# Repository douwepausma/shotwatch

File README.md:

# Shotwatch
Display the brewing time of your GAGGIA Classic Pro with Shotwatch ☕️⏱️. This handy DIY gadget allows to display the amount of seconds your GAGGIA has been running on display.
>'Shotwatch' is a combination of the words 'Espresso <ins>**Shot**</ins>' and 'Stop<ins>**watch**</ins>'

## Why?
Many times I've either forgot to start counting our lost count (counting till 20 is hard okay) for how long my shot was running for. So I thought 'why not make something that does this for me?' After some Googling I quickly found solutions to this problem online, ones that I could purchase and install myself. They were however quite expensive, and this project sounded like something I could handle myself and learn a thing or two. So I opted to do it myself. In the end I probably spend more time and money prototyping then when I would've bought a solution, but what's the fun in that?! And (spoiler alert) I even learned how to make my own pcb in this project!

## How does it work?
The Shotwatch is quite simple and consists out of only 2 components, the screen and the logic board. The logic board is hooked up in series with two wires behind the brewing switch, this turns the Shotwatch on and automatically starts counting. The number is displayed on a small OLED screen connected to the logic board. Logic board is an Arduino Pro Micro, and powered with current directly coming via the brewing switch itself. GAGGIA Classic Pro's internals are all 230 AC current, so the I created a pcb where the logic board is mounted onto that houses a transformer to get the appropriate volts and wattage.

## Bill of materials
In addition to the 3 printed parts and the Shotwatch PCB, the following parts are required. You can find all the parts below on AliExpress. Concerning the Shotwatch PCB, you can get this manufactured at PCBWay with the gerber files. And you can print the STL files for the case yourself, or find a place where you can get them printed.

|Part|Amount|
|----|------|
|HLK-10M05(10W 5V)|1x|
|Arduino Pro Micro|1x|
|Header pins 2x12|2x|
|SSD1315 Oled screen|1x|
|4pin JST female connector|1x|
|4pin JST male connector|2x|
|KF128 5.08MM pitch, 2 port screw terminal|1x|
|30cm 4 wire ribbon cable|1x|
|30cm 18 AWG cable|2x|
|Piggyback connecter (with insulation)|2x|

## Assembly
https://github.com/user-attachments/assets/8fb99642-29bd-4e3d-afc3-6cd245b8583b

## Shotwatch in action
https://github.com/user-attachments/assets/95962a83-e972-49d3-940f-4a79777042f4

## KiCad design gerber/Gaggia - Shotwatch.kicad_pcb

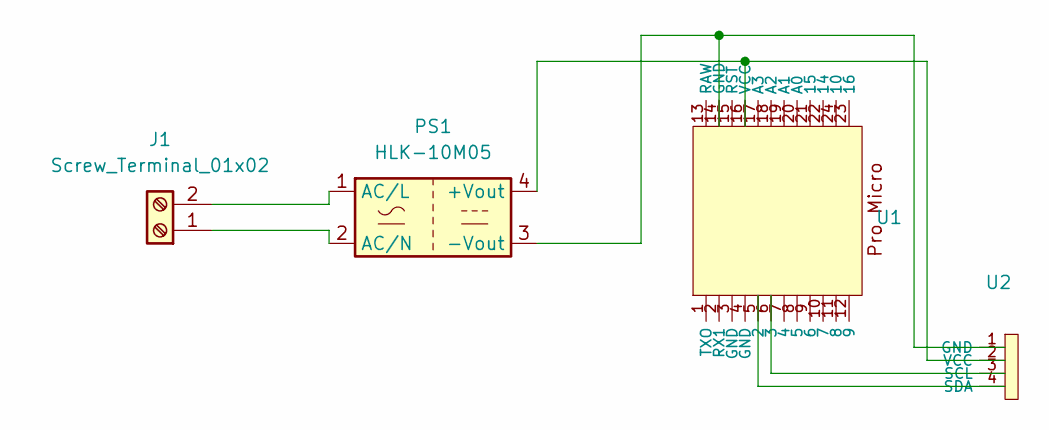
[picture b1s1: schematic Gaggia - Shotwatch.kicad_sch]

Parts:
J1: Screw_Terminal_01x02; TerminalBlock_MaiXu_MX126-5.0-02P_1x02_P5.00mm
PS1: HLK-10M05; Converter_ACDC_Hi-Link_HLK-10Mxx
U1: Pro Micro
U2: 4_Through_Hole_Pads

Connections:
unnamed: J1.1, PS1.2 (AC/N)
unnamed: J1.2, PS1.1 (AC/L)
unnamed: PS1.4 (+Vout), U1.16 (VCC), U2.2 (VCC)
unnamed: PS1.3 (-Vout), U1.14 (GND), U2.1 (GND)
unnamed: U1.5 (2), U2.4 (SDA)
unnamed: U1.6 (3), U2.3 (SCL)

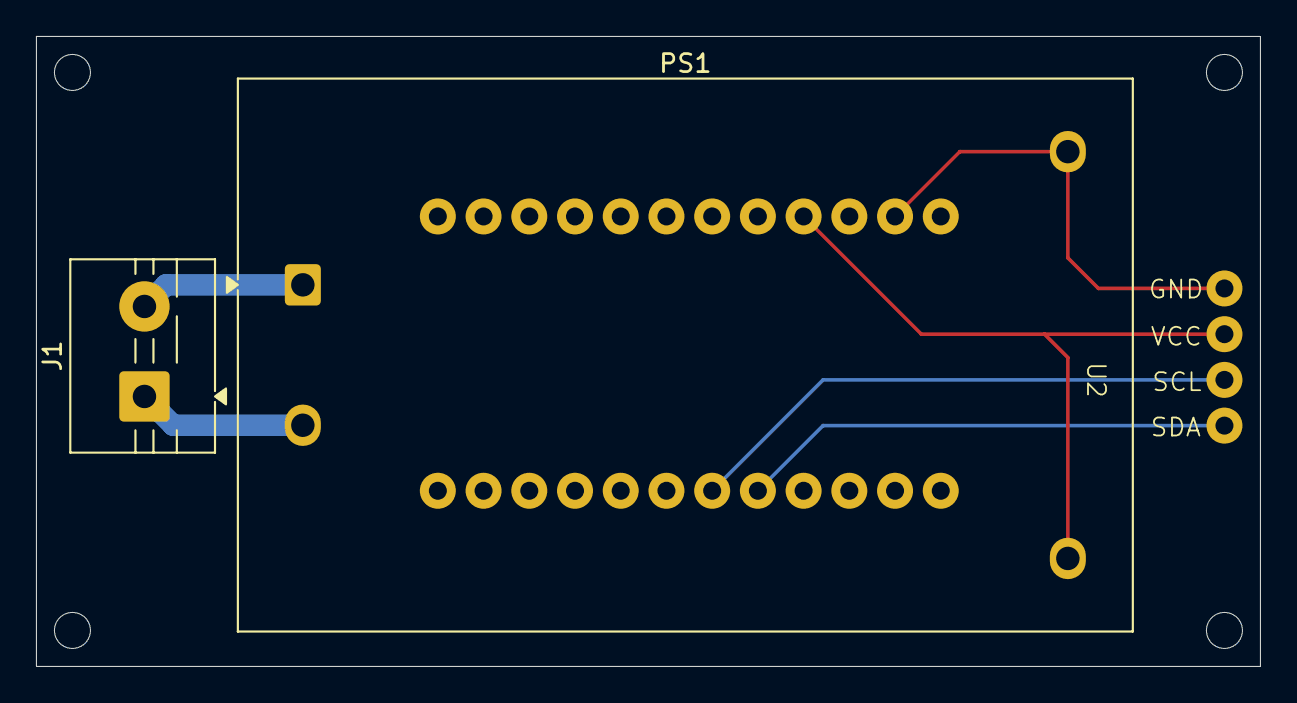
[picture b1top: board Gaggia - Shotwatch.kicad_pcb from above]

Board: 2 copper layers, 68.0 x 35.0 mm, 4 parts (1 on the bottom side), 6 nets.

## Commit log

2025-10-11 Enhance README with project overview and instructions
    Expanded README with project details and build guide.
2025-10-11 add: project files
2025-10-11 Add bill of materials to README
    Updated the README to include a bill of materials section with required parts for the Shotwatch project.
2025-10-11 change to .mov
2025-10-11 Add assembly section with link to resources
    Added assembly link to the README.
2025-10-16 improve screen case
2025-10-16 add: example video
